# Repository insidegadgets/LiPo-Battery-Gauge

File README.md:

# LiPo-Battery-Gauge
For the GBA but could work on the DMG, GBC, MGB

License: CC-BY-NC

The ATtiny48 part number to order is any of these:
ATTINY48-MMU
ATTINY48-MMUR
ATtiny48-MMH
ATtiny48-MMHR

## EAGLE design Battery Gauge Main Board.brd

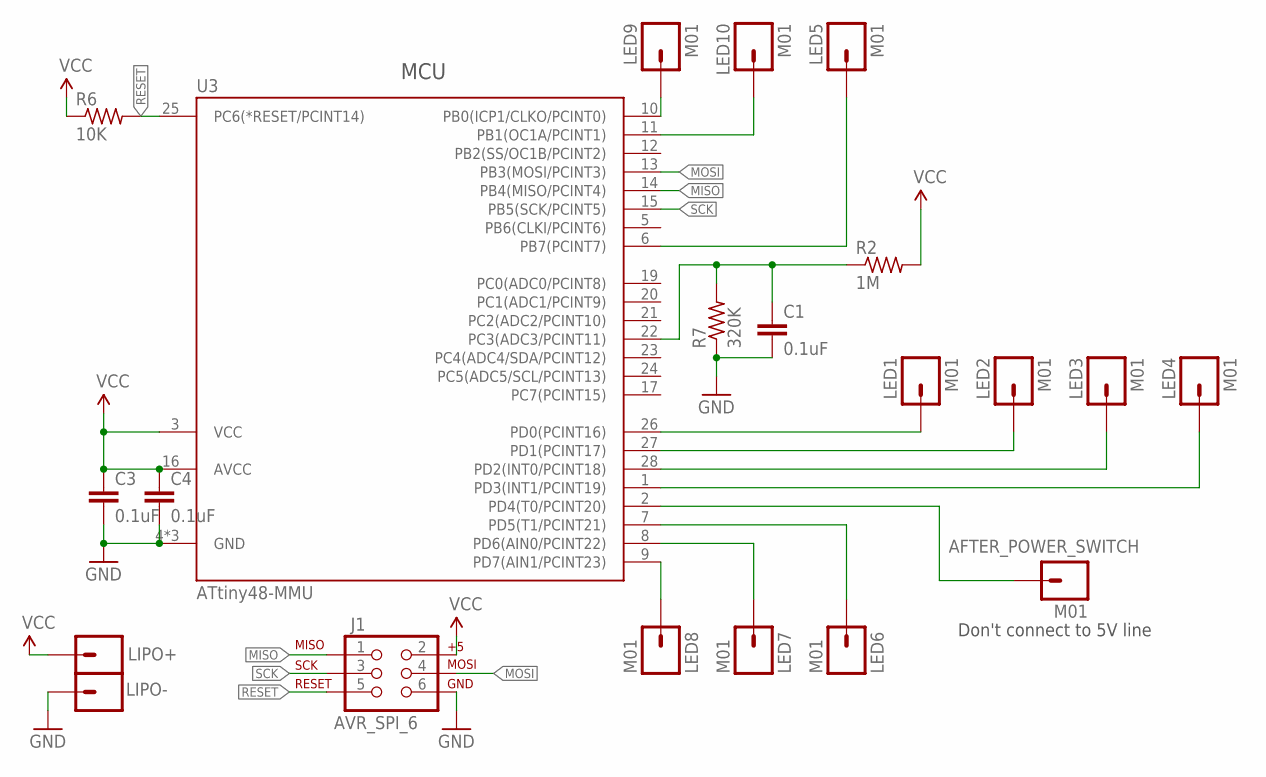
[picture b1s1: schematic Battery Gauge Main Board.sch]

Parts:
AFTER_POWER_SWITCH: M01; 1X01_SMD_SM
C1, C3, C4: 0.1uF; C0603K
J1: AVR_SPI_6; 2X3_2
LED1, LED2, LED3, LED4, LED5, LED6, LED7, LED8, LED9, LED10: M01; 1X01_SMD_SM
LIPO+: M01SMALL; 1X01_SMD_SMALL
LIPO-: M01SMALL; 1X01_SMD_SMALL
R2: 1M; R0603_S
R6: 10K; R0603_S
R7: 320K; R0603_S
U3: ATtiny48-MMU; VQFN-28

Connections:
GND: C1.2, C3.2, C4.2, J1.6, LIPO-.1, R7.1, U3.4 (GND), U3.18 (GND), U3.29 (GND)
MISO: J1.1, U3.14 (PB4(MISO/PCINT4))
MOSI: J1.4, U3.13 (PB3(MOSI/PCINT3))
unnamed: LED1.P$1, U3.26 (PD0(PCINT16))
unnamed: LED2.P$1, U3.27 (PD1(PCINT17))
unnamed: C1.1, R2.1, R7.2, U3.22 (PC3(ADC3/PCINT11))
unnamed: LED4.P$1, U3.1 (PD3(INT1/PCINT19))
unnamed: LED5.P$1, U3.6 (PB7(PCINT7))
unnamed: LED3.P$1, U3.28 (PD2(INT0/PCINT18))
unnamed: AFTER_POWER_SWITCH.P$1, U3.2 (PD4(T0/PCINT20))
unnamed: LED9.P$1, U3.10 (PB0(ICP1/CLKO/PCINT0))
unnamed: LED10.P$1, U3.11 (PB1(OC1A/PCINT1))
unnamed: LED6.P$1, U3.7 (PD5(T1/PCINT21))
unnamed: LED7.P$1, U3.8 (PD6(AIN0/PCINT22))
unnamed: LED8.P$1, U3.9 (PD7(AIN1/PCINT23))
RESET: J1.5, R6.2, U3.25 (PC6(*RESET/PCINT14))
SCK: J1.3, U3.15 (PB5(SCK/PCINT5))
VCC: C3.1, C4.1, J1.2, LIPO+.1, R2.2, R6.1, U3.3 (VCC), U3.16 (AVCC)

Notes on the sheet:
MCU
Don't connect to 5V line

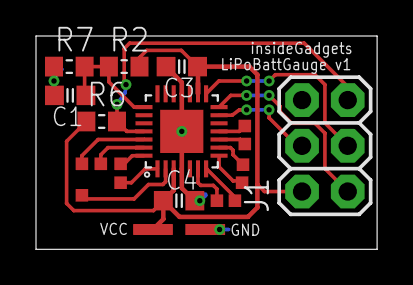
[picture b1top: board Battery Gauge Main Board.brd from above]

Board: 2 copper layers, 18.9 x 11.9 mm, 21 parts (0 on the bottom side), 18 nets.

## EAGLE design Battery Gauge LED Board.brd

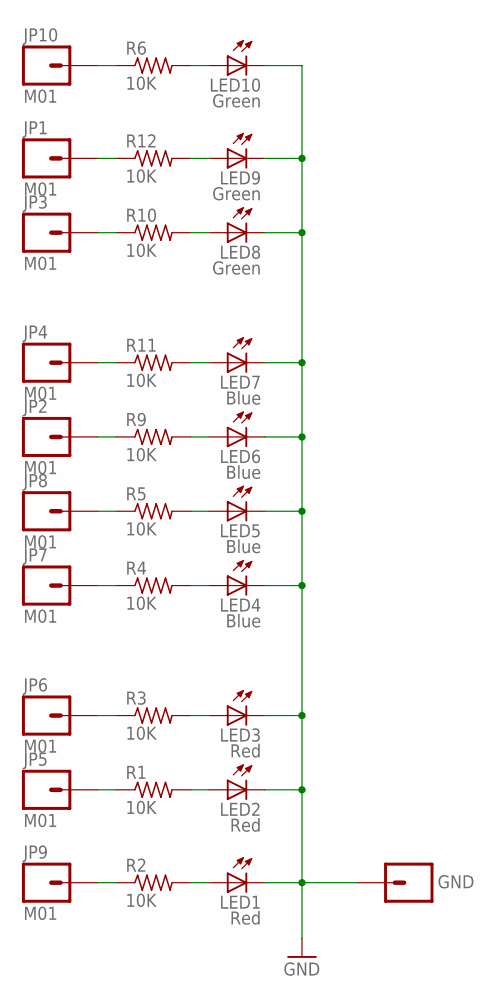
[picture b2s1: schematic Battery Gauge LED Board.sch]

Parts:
GND: M01; 1X01_SMD_SM
JP1, JP2, JP3, JP4, JP5, JP6, JP7, JP8, JP9, JP10: M01; 1X01_SMD_SM
LED1, LED2, LED3: Red; CHIPLED_1206_SLIM
LED4, LED5, LED6, LED7: Blue; CHIPLED_1206_SLIM
LED8, LED9, LED10: Green; CHIPLED_1206_SLIM
R1, R2, R3, R4, R5, R6, R9, R10, R11, R12: 10K; R0805_2

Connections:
GND: GND.P$1, LED1.C, LED2.C, LED3.C, LED4.C, LED5.C, LED6.C, LED7.C, LED8.C, LED9.C, LED10.C
unnamed: LED2.A, R1.2
unnamed: LED3.A, R3.2
unnamed: JP1.P$1, R12.1
unnamed: JP2.P$1, R9.1
unnamed: LED4.A, R4.2
unnamed: LED5.A, R5.2
unnamed: JP3.P$1, R10.1
unnamed: LED6.A, R9.2
unnamed: LED8.A, R10.2
unnamed: LED7.A, R11.2
unnamed: LED9.A, R12.2
unnamed: JP4.P$1, R11.1
unnamed: JP5.P$1, R1.1
unnamed: JP6.P$1, R3.1
unnamed: JP7.P$1, R4.1
unnamed: JP8.P$1, R5.1
unnamed: LED1.A, R2.2
unnamed: JP9.P$1, R2.1
unnamed: LED10.A, R6.2
unnamed: JP10.P$1, R6.1

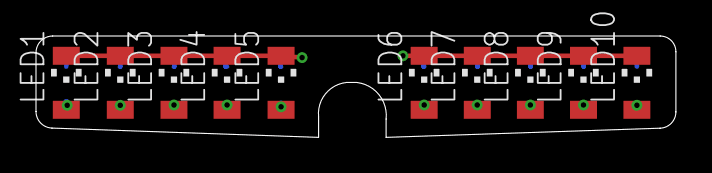
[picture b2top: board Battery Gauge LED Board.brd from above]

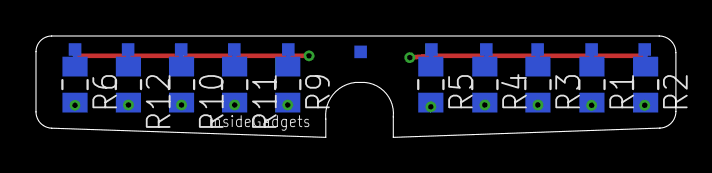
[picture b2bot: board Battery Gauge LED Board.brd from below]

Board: 2 copper layers, 35.5 x 5.6 mm, 31 parts (21 on the bottom side), 21 nets.

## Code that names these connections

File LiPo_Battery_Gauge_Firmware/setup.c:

/*
 LiPo Battery Gauge
 Version: 1.2
 Author: Alex from insideGadgets (http://www.insidegadgets.com)
 Created: 13/10/2019
 Last Modified: 1/11/2019

 */
 
#ifndef cbi
#define cbi(sfr, bit) (_SFR_BYTE(sfr) &= ~_BV(bit))
#endif
#ifndef sbi
#define sbi(sfr, bit) (_SFR_BYTE(sfr) |= _BV(bit))
#endif

#ifndef NULL
#define NULL ((void *)0)
#endif

#define LOW 0
#define HIGH 1
#define false 0
#define true 1

// Watchdog timeouts to values
#define T16MS 0
#define T32MS 1
#define T64MS 2
#define T128MS 3
#define T250MS 4
#define T500MS 5
#define T1S 6
#define T2S 7
#define T4S 8
#define T8S 9

#define POWER_ON_PIN PD4
#define batteryADCPin 3
#define LED1 PD0
#define LED2 PD1
#define LED3 PD2
#define LED4 PD3
#define LED5 PB7
#define LED6 PD5
#define LED7 PD6
#define LED8 PD7
#define LED9 PB0
#define LED10 PB1

// ADC Refs
#define REF_1_1V 0
#define REF_AVCC 1

#define DELAY_TIME 50

// Sleep
void system_sleep(void) {
	set_sleep_mode(SLEEP_MODE_PWR_DOWN); // Set sleep mode
	sleep_mode(); // System sleeps here
}

// Setup watchdog timed sequence
void setup_watchdog(uint8_t wdDelay) {
	if (wdDelay > 9) { 
		wdDelay = 9;
	}
	
	uint8_t bb = wdDelay & 7;
	if (wdDelay > 7) { 
		bb |= (1<<5);
	}
	
	cli(); // Turn interrupts off
	asm("WDR");
	
	MCUSR &= ~(1<<WDRF);
	// Start timed sequence
	WDTCSR |= (1<<WDCE) | (1<<WDE);
	// Set new watchdog timeout value
	WDTCSR = bb | (1<<WDIE);
	
	sei(); // Turn interrupts back on
}

// Turn off the Watchdog
void turn_off_watchdog(void) {
	cli(); // Turn interrupts off
	asm("WDR");
	MCUSR &= ~(1<<WDRF);
	WDTCSR |= (1<<WDCE) | (1<<WDIE);
	WDTCSR = 0;
	sei(); // Turn interrupts back on
}

// Watchdog sleep function - setup, sleep and turn off
void watchdog_sleep(uint8_t timeout) { 
	setup_watchdog(timeout);
	system_sleep();
	turn_off_watchdog();
}

// Read the ADC
int adc_read(uint8_t pin, uint8_t reference) {
	uint8_t low, high;
	
	// Set the analog reference (high two bits of ADMUX) and select the channel (low 4 bits)
	if (reference == REF_1_1V) {
		ADMUX = (pin & 0x0F); // 1.1V reference
	}
	else {
		ADMUX = (1<<REFS0) | (pin & 0x0F); // AVCC Ref
	}
	
	set_sleep_mode(SLEEP_MODE_ADC); // Set sleep mode ADC
	sleep_mode(); // System sleeps here
	
	// Read ADCL first
	low = ADCL;
	high = ADCH;
	
	// combine the two bytes
	return (high << 8) | low;
}

// Animate LEDs at start-up
void animate_leds(void) {
	_delay_ms(100);
	
	// 5 samples over 25ms
	uint16_t batteryVoltageLevel = 0;
	for (uint8_t x = 0; x < 5; x++) {
		batteryVoltageLevel += adc_read(batteryADCPin, REF_1_1V);
		_delay_ms(5);
	}
	batteryVoltageLevel = batteryVoltageLevel / 5;
	
	// Red
	if (batteryVoltageLevel >= 675) {
		PORTD |= (1<<LED1);
		_delay_ms(DELAY_TIME);
	}
	if (batteryVoltageLevel >= 720) {
		PORTD |= (1<<LED2);
		_delay_ms(DELAY_TIME);
	}
	if (batteryVoltageLevel >= 750) {
		PORTD |= (1<<LED3);
		_delay_ms(DELAY_TIME);
	}
	
	// Blue
	if (batteryVoltageLevel >= 825) {
		PORTD |= (1<<LED4);
		_delay_ms(DELAY_TIME);
	}
	if (batteryVoltageLevel >= 850) {
		PORTB |= (1<<LED5);
		_delay_ms(DELAY_TIME);
	}
	if (batteryVoltageLevel >= 875) {
		PORTD |= (1<<LED6);
		_delay_ms(DELAY_TIME);
	}
	if (batteryVoltageLevel >= 890) {
		PORTD |= (1<<LED7);
		_delay_ms(DELAY_TIME);
	}
	
	// Green
	if (batteryVoltageLevel >= 910) {
		PORTD |= (1<<LED8);
		_delay_ms(DELAY_TIME);
	}
	if (batteryVoltageLevel >= 920) {
		PORTB |= (1<<LED9);
		_delay_ms(DELAY_TIME);
	}
	if (batteryVoltageLevel >= 930) {
		PORTB |= (1<<LED10);
	}
}

// Setup
void setup(void) {
	// Turn on pull ups
	PORTB |= (1<<PB2) | (1<<PB3) | (1<<PB4) | (1<<PB5) | (1<<PB6); 
	PORTC |= (1<<PC0) | (1<<PC1) | (1<<PC2) | (1<<PC4) | (1<<PC5) | (1<<PC6) | (1<<PC7); 
	
	// Setup outputs
	DDRD |= (1<<LED1) | (1<<LED2) | (1<<LED3) | (1<<LED4) | (1<<LED6) | (1<<LED7) | (1<<LED8);
	DDRB |= (1<<LED5)  | (1<<LED9) | (1<<LED10);
	
	// Blink LEDs
	//PORTD |= (1<<LED1) | (1<<LED2) | (1<<LED3) | (1<<LED4) | (1<<LED6) | (1<<LED7) | (1<<LED8);
	//PORTB |= (1<<LED5) | (1<<LED9) | (1<<LED10);
	//_delay_ms(200);
	//PORTD &= ~((1<<LED1) | (1<<LED2) | (1<<LED3) | (1<<LED4) | (1<<LED6) | (1<<LED7) | (1<<LED8));
	//PORTB &= ~((1<<LED5) | (1<<LED9) | (1<<LED10));
	
	// Set ADC prescale factor to 8
	// 1 MHz / 8 = 125 KHz, inside the desired 50-200 KHz range.
	sbi(ADCSRA, ADPS1);
	sbi(ADCSRA, ADPS0);
	
	// Enable ADC/interrupt
	sbi(ADCSRA, ADEN);
	sbi(ADCSRA, ADIE);
	
	// Enable pin change interrupt on PD4
	sbi(PCMSK2, PCINT20);
	
	sei(); // Turn on interrupts
}

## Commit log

2019-10-13 v1.0
2019-10-13 Clean up, turn off LEDs at power on (as it sometimes happens at power off too)
2019-11-01 - Fixed interrupt bug - Used watchdog timer instead of delay for a ~1.5mA power saving
2019-11-01 Added power up animation
2019-11-12 Updated parts list
